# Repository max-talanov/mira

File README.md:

# MIRA

Исследовательская платформа для работы с мемристорными кроссбарами: чтение и программирование ячеек, формовка, умножение вектора на матрицу (VMM), спайковые модели.

Карты вставляются в слоты материнской платы. Сокет кроссбара стоит в центре, четыре карты AFE — квадратом вокруг него.

| Плата | Назначение | Проект KiCad |
|---|---|---|
| Mainboard | Материнская плата: слоты, линии каналов к сокету, разъём Zynq-модуля | [`hardware/Mainboard`](hardware/Mainboard/MIRA_Mainboard.kicad_pro) |
| AFE | Карта на 16 каналов с осциллографом тока. В комплекте четыре одинаковые карты | [`hardware/AFE`](hardware/AFE/MIRA_AFE.kicad_pro) |
| Zynq | Модуль с Zynq под сокетом: тайминг импульсов, сбор данных, USB 3 | [`hardware/Zynq`](hardware/Zynq/MIRA_Zynq.kicad_pro) |
| Crossbar | Сменная плата с сокетом под конкретный кроссбар | [`hardware/Crossbar`](hardware/Crossbar/MIRA_Crossbar.kicad_pro) |
| Forming | Карта формовки до ±10 В с ограничением тока | [`hardware/Forming`](hardware/Forming/MIRA_Forming.kicad_pro) |
| Power | Карта питания: вход 24 В, промежуточные шины, супервизор, аппаратные разрешения | [`hardware/Power`](hardware/Power/MIRA_Power.kicad_pro) |

Все 64 канала одинаковы и не привязаны к роли. Плата Crossbar сама решает, какие каналы будут BL, WL или NL. Например, на место 16×16×16 можно поставить кроссбар 32×8×8.

Требования и компоновка: [техническое задание](docs/ТЗ.md) и [3D-эскиз](docs/concept-3d.html).

Общие символы, footprint и 3D-модели лежат в [`hardware/libraries`](hardware/libraries). Каждый проект подключает их через `${KIPRJMOD}/../libraries`, поэтому папку `hardware/` нужно держать целиком.

## Версии

У каждой платы своя версия. Она хранится в переменной проекта `VERSION` (Файл → Свойства проекта → Текстовые переменные) и выводится в поле Rev штампа. Изменения описаны в `CHANGELOG.md` в папке платы.

| Версия | Когда повышать |
|---|---|
| 0.0.x | Небольшие изменения |
| 0.x.0 | Большие изменения |
| 1.0.0 | Плата доделана в KiCad |

Тег версии называется по плате, например `afe-v0.1.0`. Выпуск на производство учитывается отдельно и номер версии не меняет.

## Ветки

Каждая плата разрабатывается в своей ветке `board/<плата>`. Готовые шаги вливаются в `main` через PR.

## Лицензия

[LICENSE](LICENSE). Уведомления о сторонних библиотеках и моделях хранятся рядом с соответствующими файлами.

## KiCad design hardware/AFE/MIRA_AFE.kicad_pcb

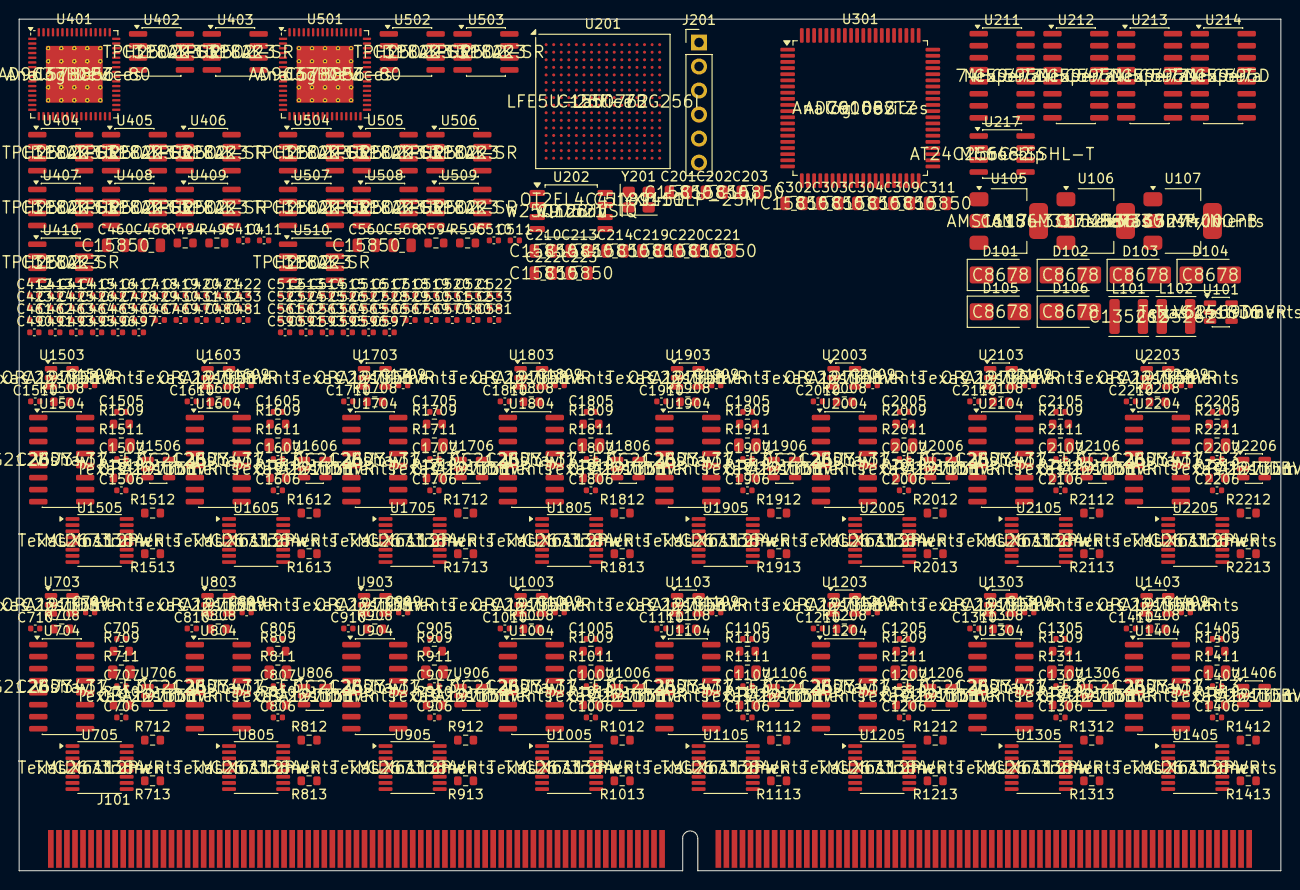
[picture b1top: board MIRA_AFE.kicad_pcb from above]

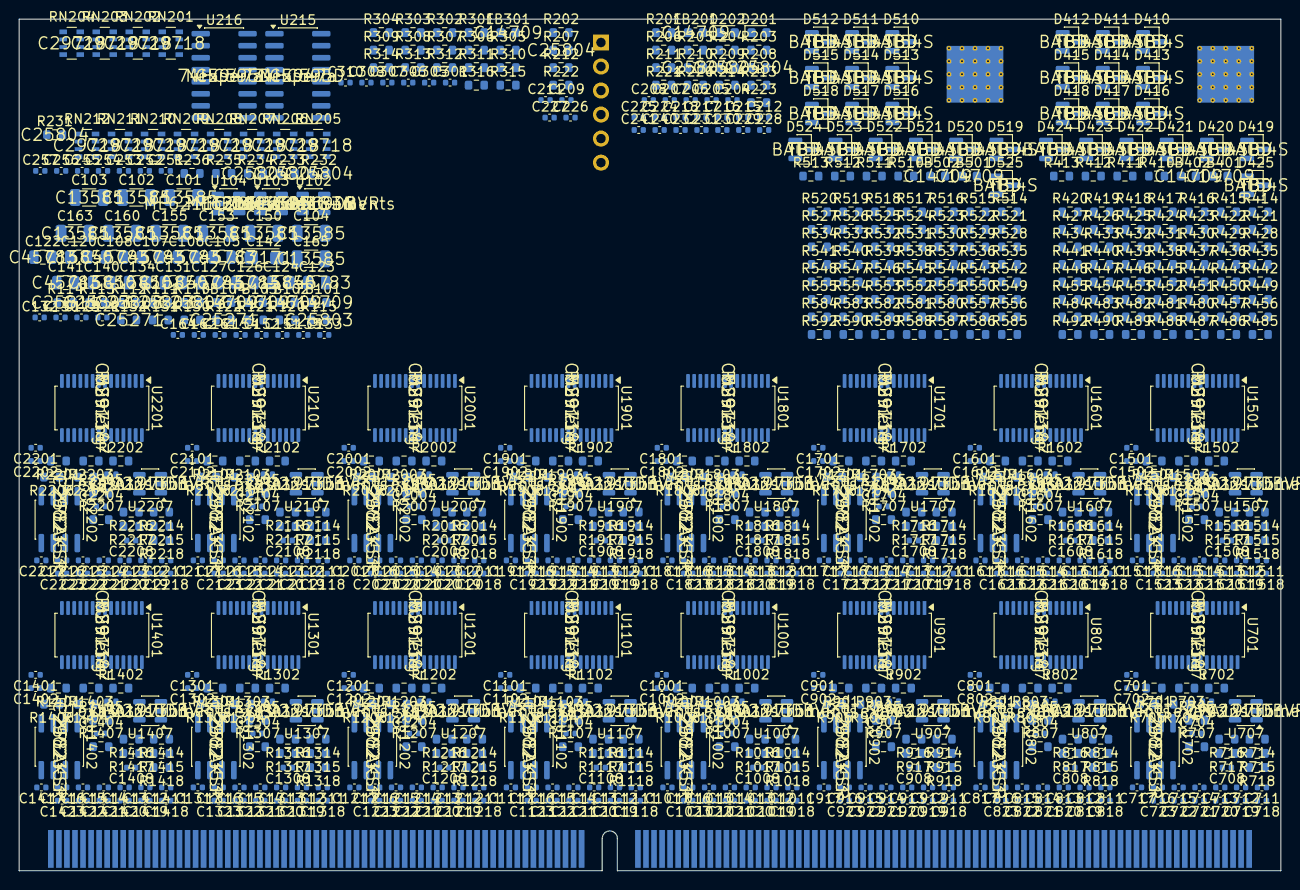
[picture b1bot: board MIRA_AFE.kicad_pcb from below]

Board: 6 copper layers, 133.3 x 90.0 mm, 1223 parts (834 on the bottom side), 771 nets, no tracks yet.

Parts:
C101, C102, C103, C104, C150, C153, C155, C160, C163, C165: 10u 50V; C_1206_3216Metric
C105, C106, C107, C108, C122, C123, C126, C127, C141: 22u; C_0805_2012Metric
C120, C124, C131, C134, C140, C201, C202, C203, C210, C213, C214, C219, C220, C221, C222, C223, C302, C303, C304, C309, C311, C460, C560: 10u; C_0805_2012Metric
C121, C125, C132, C135, C151, C154, C161, C164, C204, C205, C206, C207, C208, C209, C211, C212, C215, C216, C217, C218, C224, C225, C226, C227, C228, C229, C230, C231, C232, C240, C241, C251, C252, C253, C254, C255, C256, C257, C305, C306, C307, C308, C310, C412, C415, C418, C421, C424, C427, C430, C433, C461, C462, C463, C464, C465, C466, C467, C469, C470, C480, C481, C491, C493, C495, C496, C497, C512, C515, C518, C521, C524, C527, C530, C533, C561, C562, C563, C564, C565, C566, C567, C569, C570, C580, C581, C591, C593, C595, C596, C597, C701, C702, C703, C709, C710, C711, C712, C713, C714, C715, C716, C717, C718, C719, C720, C721, C722, C723, C801, C802, C803, C809, C810, C811, C812, C813, C814, C815, C816, C817, C818, C819, C820, C821, C822, C823, C901, C902, C903, C909, C910, C911, C912, C913, C914, C915, C916, C917, C918, C919, C920, C921, C922, C923, C1001, C1002, C1003, C1009, C1010, C1011, C1012, C1013, C1014, C1015, C1016, C1017, C1018, C1019, C1020, C1021, C1022, C1023, C1101, C1102, C1103, C1109, C1110, C1111, C1112, C1113, C1114, C1115, C1116, C1117, C1118, C1119, C1120, C1121, C1122, C1123, C1201, C1202, C1203, C1209, C1210, C1211, C1212, C1213, C1214, C1215, C1216, C1217, C1218, C1219, C1220, C1221, C1222, C1223, C1301, C1302, C1303, C1309, C1310, C1311, C1312, C1313, C1314, C1315, C1316, C1317, C1318, C1319, C1320, C1321, C1322, C1323, C1401, C1402, C1403, C1409, C1410, C1411, C1412, C1413, C1414, C1415, C1416, C1417, C1418, C1419, C1420, C1421, C1422, C1423, C1501, C1502, C1503, C1509, C1510, C1511, C1512, C1513, C1514, C1515, C1516, C1517, C1518, C1519, C1520, C1521, C1522, C1523, C1601, C1602, C1603, C1609, C1610, C1611, C1612, C1613, C1614, C1615, C1616, C1617, C1618, C1619, C1620, C1621, C1622, C1623, C1701, C1702, C1703, C1709, C1710, C1711, C1712, C1713, C1714, C1715, C1716, C1717, C1718, C1719, C1720, C1721, C1722, C1723, C1801, C1802, C1803, C1809, C1810, C1811, C1812, C1813, C1814, C1815, C1816, C1817, C1818, C1819, C1820, C1821, C1822, C1823, C1901, C1902, C1903, C1909, C1910, C1911, C1912, C1913, C1914, C1915, C1916, C1917, C1918, C1919, C1920, C1921, C1922, C1923, C2001, C2002, C2003, C2009, C2010, C2011, C2012, C2013, C2014, C2015, C2016, C2017, C2018, C2019, C2020, C2021, C2022, C2023, C2101, C2102, C2103, C2109, C2110, C2111, C2112, C2113, C2114, C2115, C2116, C2117, C2118, C2119, C2120, C2121, C2122, C2123, C2201, C2202, C2203, C2209, C2210, C2211, C2212, C2213, C2214, C2215, C2216, C2217, C2218, C2219, C2220, C2221, C2222, C2223: 100n; C_0402_1005Metric
C130, C133, C490, C590: 1u; C_0402_1005Metric
C142: 10u tant.; CP_EIA-3216-18_Kemet-A
C152, C162: 1u 25V; C_0402_1005Metric
C301: 100n X8R; C_0402_1005Metric
C410, C413, C416, C419, C422, C425, C428, C431, C510, C513, C516, C519, C522, C525, C528, C531: 22p C0G; C_0402_1005Metric
C411, C414, C417, C420, C423, C426, C429, C432, C511, C514, C517, C520, C523, C526, C529, C532: 150p C0G; C_0402_1005Metric
C468, C568: 4.7u; C_0805_2012Metric
C704, C804, C904, C1004, C1104, C1204, C1304, C1404, C1504, C1604, C1704, C1804, C1904, C2004, C2104, C2204: 2.2p C0G; C_0402_1005Metric
C705, C805, C905, C1005, C1105, C1205, C1305, C1405, C1505, C1605, C1705, C1805, C1905, C2005, C2105, C2205: 47p C0G; C_0402_1005Metric
C706, C806, C906, C1006, C1106, C1206, C1306, C1406, C1506, C1606, C1706, C1806, C1906, C2006, C2106, C2206: TBD; C_0402_1005Metric
C707, C807, C907, C1007, C1107, C1207, C1307, C1407, C1507, C1607, C1707, C1807, C1907, C2007, C2107, C2207: 0.5p C0G; C_0402_1005Metric
C708, C808, C908, C1008, C1108, C1208, C1308, C1408, C1508, C1608, C1708, C1808, C1908, C2008, C2108, C2208: 1n C0G; C_0402_1005Metric
D101, D102, D103, D104, D105, D106: SS34; D_SMA
D201, D202: green; LED_0603_1608Metric
D410, D411, D412, D413, D414, D415, D416, D417, D418, D419, D420, D421, D422, D423, D424, D425, D510, D511, D512, D513, D514, D515, D516, D517, D518, D519, D520, D521, D522, D523, D524, D525: BAT54S; SOT-23
FB101, FB102, FB103, FB104, FB201, FB301, FB401, FB402, FB501, FB502: BLM18PG121SN1D; L_0603_1608Metric
J101: DIMM-288 card edge; DIMM288_CardEdge
J201: JTAG_1x6; PinHeader_1x06_P2.54mm_Vertical
L101, L102: 2.2uH; L_Sunlord_SWPA4020S
R110, R111, R113, R115: 100k; R_0603_1608Metric
R112: 120k; R_0603_1608Metric
R114: 200k; R_0603_1608Metric
R120, R130: 120R 1%; R_0603_1608Metric
R121, R131: 1.33k 1%; R_0603_1608Metric
R122, R132: 1R; R_0603_1608Metric
R201, R202, R203, R204, R206, R211, R212, R213, R214, R235, R236: 4.7k; R_0603_1608Metric
R205, R222, R223, R301, R302, R303, R304, R305, R306, R307, R308, R309, R310, R311, R312, R313, R314, R315, R316, R481, R483, R485, R487, R489, R581, R583, R585, R587, R589, R713, R718, R813, R818, R913, R918, R1013, R1018, R1113, R1118, R1213, R1218, R1313, R1318, R1413, R1418, R1513, R1518, R1613, R1618, R1713, R1718, R1813, R1818, R1913, R1918, R2013, R2018, R2113, R2118, R2213, R2218: 1k; R_0603_1608Metric
R207, R208, R209, R210, R231, R232, R233, R234: 10k; R_0603_1608Metric
R220: 33R; R_0603_1608Metric
R221: 22R; R_0603_1608Metric
R410, R416, R422, R428, R434, R440, R446, R452, R495, R510, R516, R522, R528, R534, R540, R546, R552, R595: 10.7k 1%; R_0603_1608Metric
R411, R412, R413, R417, R418, R419, R423, R424, R425, R429, R430, R431, R435, R436, R437, R441, R442, R443, R447, R448, R449, R453, R454, R455, R494, R511, R512, R513, R517, R518, R519, R523, R524, R525, R529, R530, R531, R535, R536, R537, R541, R542, R543, R547, R548, R549, R553, R554, R555, R594: 1k 1%; R_0603_1608Metric
R414, R415, R420, R421, R426, R427, R432, R433, R438, R439, R444, R445, R450, R451, R456, R457, R514, R515, R520, R521, R526, R527, R532, R533, R538, R539, R544, R545, R550, R551, R556, R557: 49.9R; R_0603_1608Metric
R480, R580: 100R; R_0603_1608Metric
R482, R484, R486, R488, R490, R582, R584, R586, R588, R590: 1.2k; R_0603_1608Metric
R492, R592: 10k 1%; R_0603_1608Metric
R701, R801, R901, R1001, R1101, R1201, R1301, R1401, R1501, R1601, R1701, R1801, R1901, R2001, R2101, R2201: 19.1k 1%; R_0603_1608Metric
R702, R703, R802, R803, R902, R903, R1002, R1003, R1102, R1103, R1202, R1203, R1302, R1303, R1402, R1403, R1502, R1503, R1602, R1603, R1702, R1703, R1802, R1803, R1902, R1903, R2002, R2003, R2102, R2103, R2202, R2203: 499 0.1%; R_0603_1608Metric
R704, R706, R714, R715, R716, R717, R804, R806, R814, R815, R816, R817, R904, R906, R914, R915, R916, R917, R1004, R1006, R1014, R1015, R1016, R1017, R1104, R1106, R1114, R1115, R1116, R1117, R1204, R1206, R1214, R1215, R1216, R1217, R1304, R1306, R1314, R1315, R1316, R1317, R1404, R1406, R1414, R1415, R1416, R1417, R1504, R1506, R1514, R1515, R1516, R1517, R1604, R1606, R1614, R1615, R1616, R1617, R1704, R1706, R1714, R1715, R1716, R1717, R1804, R1806, R1814, R1815, R1816, R1817, R1904, R1906, R1914, R1915, R1916, R1917, R2004, R2006, R2014, R2015, R2016, R2017, R2104, R2106, R2114, R2115, R2116, R2117, R2204, R2206, R2214, R2215, R2216, R2217: 10k 0.1%; R_0603_1608Metric
R705, R707, R805, R807, R905, R907, R1005, R1007, R1105, R1107, R1205, R1207, R1305, R1307, R1405, R1407, R1505, R1507, R1605, R1607, R1705, R1707, R1805, R1807, R1905, R1907, R2005, R2007, R2105, R2107, R2205, R2207: 24.9k 0.1%; R_0603_1608Metric
R708, R808, R908, R1008, R1108, R1208, R1308, R1408, R1508, R1608, R1708, R1808, R1908, R2008, R2108, R2208: 1k 0.1%; R_0603_1608Metric
R709, R809, R909, R1009, R1109, R1209, R1309, R1409, R1509, R1609, R1709, R1809, R1909, R2009, R2109, R2209: 20k 0.1%; R_0603_1608Metric
R710, R810, R910, R1010, R1110, R1210, R1310, R1410, R1510, R1610, R1710, R1810, R1910, R2010, R2110, R2210: 2M 0.1%; R_0603_1608Metric
R711, R811, R911, R1011, R1111, R1211, R1311, R1411, R1511, R1611, R1711, R1811, R1911, R2011, R2111, R2211: 200M 1%; R_0805_2012Metric
R712, R812, R912, R1012, R1112, R1212, R1312, R1412, R1512, R1612, R1712, R1812, R1912, R2012, R2112, R2212: 10M; R_0603_1608Metric
RN201, RN202, RN203, RN204, RN205, RN206, RN207, RN208, RN209, RN210, RN211, RN212: 10k ×4; R_Array_Convex_4x0603
U101, U102: TLV62569DBVR; SOT-23-5
U103: ME6211C25M5G-N; SOT-23-5
U104: ME6211C28M5G-N; SOT-23-5
U105: AMS1117-3.3; SOT-223-3_TabPin2
U106: LM317MBSTT3G; SOT-223-3_TabPin2
U107: LM337IMP/NOPB; SOT-223-3_TabPin2
U201: LFE5U-25F-7BG256I; BGA-256_14.0x14.0mm_Layout16x16_P0.8mm_Ball0.45mm_Pad0.32mm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
U202: W25Q128JVSIQ; SOIC-8_5.3x5.3mm_P1.27mm
U211, U212, U213, U214, U215, U216: 74HC595D; SOIC-16_3.9x9.9mm_P1.27mm
U217: AT24C256C-SSHL-T; SOIC-8_3.9x4.9mm_P1.27mm
U301: AD7616BSTZ; LQFP-80_14x14mm_P0.65mm
U401, U501: AD9637BCPZ-80; QFN-64-1EP_9x9mm_P0.5mm_EP6x6mm_ThermalVias
U402, U403, U404, U405, U406, U407, U408, U409, U410, U502, U503, U504, U505, U506, U507, U508, U509, U510: TPH2502-SR; SOIC-8_3.9x4.9mm_P1.27mm
U701, U801, U901, U1001, U1101, U1201, U1301, U1401, U1501, U1601, U1701, U1801, U1901, U2001, U2101, U2201: MS9714; TSSOP-28_4.4x9.7mm_P0.65mm
U702, U802, U902, U1002, U1102, U1202, U1302, U1402, U1502, U1602, U1702, U1802, U1902, U2002, U2102, U2202: TP2582-SR; SOIC-8_3.9x4.9mm_P1.27mm
U703, U706, U707, U803, U806, U807, U903, U906, U907, U1003, U1006, U1007, U1103, U1106, U1107, U1203, U1206, U1207, U1303, U1306, U1307, U1403, U1406, U1407, U1503, U1506, U1507, U1603, U1606, U1607, U1703, U1706, U1707, U1803, U1806, U1807, U1903, U1906, U1907, U2003, U2006, U2007, U2103, U2106, U2107, U2203, U2206, U2207: OPA197IDBVR; SOT-23-5
U704, U804, U904, U1004, U1104, U1204, U1304, U1404, U1504, U1604, U1704, U1804, U1904, U2004, U2104, U2204: DG212BDY-T1-E3; SOIC-16_3.9x9.9mm_P1.27mm
U705, U805, U905, U1005, U1105, U1205, U1305, U1405, U1505, U1605, U1705, U1805, U1905, U2005, U2105, U2205: TMUX6112PWR; TSSOP-16_4.4x5mm_P0.65mm
Y201: OT2EL4C4JI-111OLP-25M; Oscillator_SMD_Abracon_ASE-4Pin_3.2x2.5mm

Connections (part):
+1V1: C122.1, C123.1, C201.1, C202.1, C203.1, C204.1, C205.1, C206.1, C207.1, C208.1, C209.1, L101.2, R111.1, U201.G6, U201.G7, U201.G9, U201.L8, U201.L9, U201.L10
+1V8: C126.1, C127.1, FB401.2, FB402.2, FB501.2, FB502.2, L102.2, R114.1
+2V5: C131.1, C132.1, C213.1, C214.1, C215.1, C216.1, C217.1, C218.1, FB201.1, U103.5, U201.H6, U201.H7, U201.H11, U201.J11
+2V8: C134.1, C135.1, C412.1, C415.1, C418.1, C421.1, C424.1, C427.1, C430.1, C433.1, C497.1, C512.1, C515.1, C518.1, C521.1, C524.1, C527.1, C530.1, C533.1, C597.1, U104.5, U402.8, U403.8, U404.8, U405.8, U406.8, U407.8, U408.8, U409.8, U410.8, U502.8, U503.8, U504.8, U505.8, U506.8, U507.8, U508.8, U509.8, U510.8
+3.3VA: C141.1, C142.1, C702.2, C722.1, C723.1, C802.2, C822.1, C823.1, C902.2, C922.1, C923.1, C1002.2, C1022.1, C1023.1, C1102.2, C1122.1, C1123.1, C1202.2, C1222.1, C1223.1, C1302.2, C1322.1, C1323.1, C1402.2, C1422.1, C1423.1, C1502.2, C1522.1, C1523.1, C1602.2, C1622.1, C1623.1, C1702.2, C1722.1, C1723.1, C1802.2, C1822.1, C1823.1, C1902.2, C1922.1, C1923.1, C2002.2, C2022.1, C2023.1, C2102.2, C2122.1, C2123.1, C2202.2, C2222.1, C2223.1, U105.2, U701.24, U701.27, U801.24, U801.27, U901.24, U901.27, U1001.24, U1001.27, U1101.24, U1101.27, U1201.24, U1201.27, U1301.24, U1301.27, U1401.24, U1401.27, U1501.24, U1501.27, U1601.24, U1601.27, U1701.24, U1701.27, U1801.24, U1801.27, U1901.24, U1901.27, U2001.24, U2001.27, U2101.24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
+3V3: C107.1, C108.1, C130.1, C133.1, C219.1, C220.1, C221.1, C222.1, C223.1, C224.1, C225.1, C226.1, C227.1, C228.1, C229.1, C230.1, C231.1, C232.1, C240.2, C241.1, C251.1, C252.1, C253.1, C254.1, C255.1, C256.1, C257.1, C310.1, C311.1, D104.1, FB104.2, J201.1, R201.1, R202.1, R203.1, R204.1, R205.1, R206.1, R207.1, R208.1, R209.1, R210.1, R211.1, R212.1, R213.1, R231.1, R232.1, R233.1, R234.1, R235.1, R236.1, U103.1, U103.3, U104.1, U104.3, U201.F6, U201.F7, U201.F10, U201.F11, U201.J6, U201.J7, U201.K11, U201.L6, U201.L11, U202.8, U211.10, U211.16, U212.10, U212.16, U213.10, U213.16, U214.10, U214.16, U215.10, U215.16, U216.10, U216.16, U217.8, U301.35, U301.40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
+5V: C105.1, C106.1, C120.1, C121.1, C124.1, C125.1, C140.1, C721.1, C821.1, C921.1, C1021.1, C1121.1, C1221.1, C1321.1, C1421.1, C1521.1, C1621.1, C1721.1, C1821.1, C1921.1, C2021.1, C2121.1, C2221.1, D103.1, FB103.2, FB301.1, R110.1, R113.1, U101.4, U102.4, U105.3, U704.12, U804.12, U904.12, U1004.12, U1104.12, U1204.12, U1304.12, U1404.12, U1504.12, U1604.12, U1704.12, U1804.12, U1904.12, U2004.12, U2104.12, U2204.12
+5VA: C305.1, C306.1, C307.1, C308.1, C309.1, FB301.2, U301.6, U301.15, U301.30, U301.71
+15V: C153.1, C154.1, C709.1, C711.1, C713.1, C715.1, C717.1, C719.1, C809.1, C811.1, C813.1, C815.1, C817.1, C819.1, C909.1, C911.1, C913.1, C915.1, C917.1, C919.1, C1009.1, C1011.1, C1013.1, C1015.1, C1017.1, C1019.1, C1109.1, C1111.1, C1113.1, C1115.1, C1117.1, C1119.1, C1209.1, C1211.1, C1213.1, C1215.1, C1217.1, C1219.1, C1309.1, C1311.1, C1313.1, C1315.1, C1317.1, C1319.1, C1409.1, C1411.1, C1413.1, C1415.1, C1417.1, C1419.1, C1509.1, C1511.1, C1513.1, C1515.1, C1517.1, C1519.1, C1609.1, C1611.1, C1613.1, C1615.1, C1617.1, C1619.1, C1709.1, C1711.1, C1713.1, C1715.1, C1717.1, C1719.1, C1809.1, C1811.1, C1813.1, C1815.1, C1817.1, C1819.1, C1909.1, C1911.1, C1913.1, C1915.1, C1917.1, C1919.1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
-15V: C163.1, C164.1, C710.2, C712.2, C714.2, C716.2, C718.2, C720.2, C810.2, C812.2, C814.2, C816.2, C818.2, C820.2, C910.2, C912.2, C914.2, C916.2, C918.2, C920.2, C1010.2, C1012.2, C1014.2, C1016.2, C1018.2, C1020.2, C1110.2, C1112.2, C1114.2, C1116.2, C1118.2, C1120.2, C1210.2, C1212.2, C1214.2, C1216.2, C1218.2, C1220.2, C1310.2, C1312.2, C1314.2, C1316.2, C1318.2, C1320.2, C1410.2, C1412.2, C1414.2, C1416.2, C1418.2, C1420.2, C1510.2, C1512.2, C1514.2, C1516.2, C1518.2, C1520.2, C1610.2, C1612.2, C1614.2, C1616.2, C1618.2, C1620.2, C1710.2, C1712.2, C1714.2, C1716.2, C1718.2, C1720.2, C1810.2, C1812.2, C1814.2, C1816.2, C1818.2, C1820.2, C1910.2, C1912.2, C1914.2, C1916.2, C1918.2, C1920.2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
/Channels/BLEED0: U201.L16, U705.9
/Channels/BLEED1: U201.L15, U805.9
/Channels/BLEED2: U201.M16, U905.9
/Channels/BLEED3: U201.M15, U1005.9
/Channels/BLEED4: U201.K13, U1105.9
/Channels/BLEED5: U201.K12, U1205.9
/Channels/BLEED6: U201.L13, U1305.9
/Channels/BLEED7: U201.L12, U1405.9
/Channels/BLEED8: U201.N16, U1505.9
/Channels/BLEED9: U201.P15, U1605.9
/Channels/BLEED10: U201.L14, U1705.9
/Channels/BLEED11: U201.M14, U1805.9
/Channels/BLEED12: U201.P16, U1905.9
/Channels/BLEED13: U201.R16, U2005.9
/Channels/BLEED14: U201.M13, U2105.9
/Channels/BLEED15: U201.N14, U2205.9
/Channels/CH0/F: C705.2, C706.2, C707.2, R708.2, R709.2, R710.2, R711.2, R712.2, U705.3, U706.3
/Channels/CH0/FB: R714.1, U706.1, U706.4
/Channels/CH0/IA: R702.1, R706.1, U701.22
/Channels/CH0/IB: R703.1, R704.1, U701.21
/Channels/CH0/OUT: C707.1, R711.1, R716.1, U703.1, U704.3, U704.11, U704.14
/Channels/CH0/SENSE: R712.1, U703.4, U705.14
/Channels/CH0/VSET: C704.2, R705.2, U702.1, U703.3
/Channels/CH1/F: C805.2, C806.2, C807.2, R808.2, R809.2, R810.2, R811.2, R812.2, U805.3, U806.3
/Channels/CH1/FB: R814.1, U806.1, U806.4
/Channels/CH1/IA: R802.1, R806.1, U801.22
/Channels/CH1/IB: R803.1, R804.1, U801.21
/Channels/CH1/OUT: C807.1, R811.1, R816.1, U803.1, U804.3, U804.11, U804.14
/Channels/CH1/SENSE: R812.1, U803.4, U805.14
/Channels/CH1/VSET: C804.2, R805.2, U802.1, U803.3
/Channels/CH2/F: C905.2, C906.2, C907.2, R908.2, R909.2, R910.2, R911.2, R912.2, U905.3, U906.3
/Channels/CH2/FB: R914.1, U906.1, U906.4
/Channels/CH2/IA: R902.1, R906.1, U901.22
/Channels/CH2/IB: R903.1, R904.1, U901.21
/Channels/CH2/OUT: C907.1, R911.1, R916.1, U903.1, U904.3, U904.11, U904.14
/Channels/CH2/SENSE: R912.1, U903.4, U905.14
/Channels/CH2/VSET: C904.2, R905.2, U902.1, U903.3
/Channels/CH3/F: C1005.2, C1006.2, C1007.2, R1008.2, R1009.2, R1010.2, R1011.2, R1012.2, U1005.3, U1006.3
/Channels/CH3/FB: R1014.1, U1006.1, U1006.4
/Channels/CH3/IA: R1002.1, R1006.1, U1001.22
/Channels/CH3/IB: R1003.1, R1004.1, U1001.21
/Channels/CH3/OUT: C1007.1, R1011.1, R1016.1, U1003.1, U1004.3, U1004.11, U1004.14
/Channels/CH3/SENSE: R1012.1, U1003.4, U1005.14
/Channels/CH3/VSET: C1004.2, R1005.2, U1002.1, U1003.3
/Channels/CH4/F: C1105.2, C1106.2, C1107.2, R1108.2, R1109.2, R1110.2, R1111.2, R1112.2, U1105.3, U1106.3
/Channels/CH4/FB: R1114.1, U1106.1, U1106.4
/Channels/CH4/IA: R1102.1, R1106.1, U1101.22
/Channels/CH4/IB: R1103.1, R1104.1, U1101.21
/Channels/CH4/OUT: C1107.1, R1111.1, R1116.1, U1103.1, U1104.3, U1104.11, U1104.14
/Channels/CH4/SENSE: R1112.1, U1103.4, U1105.14
/Channels/CH4/VSET: C1104.2, R1105.2, U1102.1, U1103.3
/Channels/CH5/F: C1205.2, C1206.2, C1207.2, R1208.2, R1209.2, R1210.2, R1211.2, R1212.2, U1205.3, U1206.3
/Channels/CH5/FB: R1214.1, U1206.1, U1206.4
/Channels/CH5/IA: R1202.1, R1206.1, U1201.22
/Channels/CH5/IB: R1203.1, R1204.1, U1201.21
/Channels/CH5/OUT: C1207.1, R1211.1, R1216.1, U1203.1, U1204.3, U1204.11, U1204.14
/Channels/CH5/SENSE: R1212.1, U1203.4, U1205.14
/Channels/CH5/VSET: C1204.2, R1205.2, U1202.1, U1203.3
/Channels/CH6/F: C1305.2, C1306.2, C1307.2, R1308.2, R1309.2, R1310.2, R1311.2, R1312.2, U1305.3, U1306.3
/Channels/CH6/FB: R1314.1, U1306.1, U1306.4
/Channels/CH6/IA: R1302.1, R1306.1, U1301.22
/Channels/CH6/IB: R1303.1, R1304.1, U1301.21
/Channels/CH6/OUT: C1307.1, R1311.1, R1316.1, U1303.1, U1304.3, U1304.11, U1304.14
/Channels/CH6/SENSE: R1312.1, U1303.4, U1305.14
/Channels/CH6/VSET: C1304.2, R1305.2, U1302.1, U1303.3
/Channels/CH7/F: C1405.2, C1406.2, C1407.2, R1408.2, R1409.2, R1410.2, R1411.2, R1412.2, U1405.3, U1406.3
/Channels/CH7/FB: R1414.1, U1406.1, U1406.4
/Channels/CH7/IA: R1402.1, R1406.1, U1401.22
/Channels/CH7/IB: R1403.1, R1404.1, U1401.21
/Channels/CH7/OUT: C1407.1, R1411.1, R1416.1, U1403.1, U1404.3, U1404.11, U1404.14
/Channels/CH7/SENSE: R1412.1, U1403.4, U1405.14
/Channels/CH7/VSET: C1404.2, R1405.2, U1402.1, U1403.3
/Channels/CH8/F: C1505.2, C1506.2, C1507.2, R1508.2, R1509.2, R1510.2, R1511.2, R1512.2, U1505.3, U1506.3
/Channels/CH8/FB: R1514.1, U1506.1, U1506.4
/Channels/CH8/IA: R1502.1, R1506.1, U1501.22
/Channels/CH8/IB: R1503.1, R1504.1, U1501.21
/Channels/CH8/OUT: C1507.1, R1511.1, R1516.1, U1503.1, U1504.3, U1504.11, U1504.14
/Channels/CH8/SENSE: R1512.1, U1503.4, U1505.14
/Channels/CH8/VSET: C1504.2, R1505.2, U1502.1, U1503.3
/Channels/CH9/F: C1605.2, C1606.2, C1607.2, R1608.2, R1609.2, R1610.2, R1611.2, R1612.2, U1605.3, U1606.3
/Channels/CH9/FB: R1614.1, U1606.1, U1606.4
/Channels/CH9/IA: R1602.1, R1606.1, U1601.22
/Channels/CH9/IB: R1603.1, R1604.1, U1601.21
/Channels/CH9/OUT: C1607.1, R1611.1, R1616.1, U1603.1, U1604.3, U1604.11, U1604.14
/Channels/CH9/SENSE: R1612.1, U1603.4, U1605.14
/Channels/CH9/VSET: C1604.2, R1605.2, U1602.1, U1603.3
/Channels/CH10/F: C1705.2, C1706.2, C1707.2, R1708.2, R1709.2, R1710.2, R1711.2, R1712.2, U1705.3, U1706.3
/Channels/CH10/FB: R1714.1, U1706.1, U1706.4
/Channels/CH10/IA: R1702.1, R1706.1, U1701.22
/Channels/CH10/IB: R1703.1, R1704.1, U1701.21
/Channels/CH10/OUT: C1707.1, R1711.1, R1716.1, U1703.1, U1704.3, U1704.11, U1704.14
/Channels/CH10/SENSE: R1712.1, U1703.4, U1705.14
/Channels/CH10/VSET: C1704.2, R1705.2, U1702.1, U1703.3
/Channels/CH11/F: C1805.2, C1806.2, C1807.2, R1808.2, R1809.2, R1810.2, R1811.2, R1812.2, U1805.3, U1806.3
/Channels/CH11/FB: R1814.1, U1806.1, U1806.4
/Channels/CH11/IA: R1802.1, R1806.1, U1801.22
/Channels/CH11/IB: R1803.1, R1804.1, U1801.21
/Channels/CH11/OUT: C1807.1, R1811.1, R1816.1, U1803.1, U1804.3, U1804.11, U1804.14
/Channels/CH11/SENSE: R1812.1, U1803.4, U1805.14
/Channels/CH11/VSET: C1804.2, R1805.2, U1802.1, U1803.3
/Channels/CH12/F: C1905.2, C1906.2, C1907.2, R1908.2, R1909.2, R1910.2, R1911.2, R1912.2, U1905.3, U1906.3
/Channels/CH12/FB: R1914.1, U1906.1, U1906.4
/Channels/CH12/IA: R1902.1, R1906.1, U1901.22
/Channels/CH12/IB: R1903.1, R1904.1, U1901.21
/Channels/CH12/OUT: C1907.1, R1911.1, R1916.1, U1903.1, U1904.3, U1904.11, U1904.14
/Channels/CH12/SENSE: R1912.1, U1903.4, U1905.14
/Channels/CH12/VSET: C1904.2, R1905.2, U1902.1, U1903.3
/Channels/CH13/F: C2005.2, C2006.2, C2007.2, R2008.2, R2009.2, R2010.2, R2011.2, R2012.2, U2005.3, U2006.3
/Channels/CH13/FB: R2014.1, U2006.1, U2006.4
/Channels/CH13/IA: R2002.1, R2006.1, U2001.22
/Channels/CH13/IB: R2003.1, R2004.1, U2001.21
/Channels/CH13/OUT: C2007.1, R2011.1, R2016.1, U2003.1, U2004.3, U2004.11, U2004.14
/Channels/CH13/SENSE: R2012.1, U2003.4, U2005.14
/Channels/CH13/VSET: C2004.2, R2005.2, U2002.1, U2003.3
/Channels/CH14/F: C2105.2, C2106.2, C2107.2, R2108.2, R2109.2, R2110.2, R2111.2, R2112.2, U2105.3, U2106.3
/Channels/CH14/FB: R2114.1, U2106.1, U2106.4
/Channels/CH14/IA: R2102.1, R2106.1, U2101.22
/Channels/CH14/IB: R2103.1, R2104.1, U2101.21
/Channels/CH14/OUT: C2107.1, R2111.1, R2116.1, U2103.1, U2104.3, U2104.11, U2104.14
/Channels/CH14/SENSE: R2112.1, U2103.4, U2105.14
/Channels/CH14/VSET: C2104.2, R2105.2, U2102.1, U2103.3
/Channels/CH15/F: C2205.2, C2206.2, C2207.2, R2208.2, R2209.2, R2210.2, R2211.2, R2212.2, U2205.3, U2206.3
/Channels/CH15/FB: R2214.1, U2206.1, U2206.4
/Channels/CH15/IA: R2202.1, R2206.1, U2201.22
/Channels/CH15/IB: R2203.1, R2204.1, U2201.21
/Channels/CH15/OUT: C2207.1, R2211.1, R2216.1, U2203.1, U2204.3, U2204.11, U2204.14
/Channels/CH15/SENSE: R2212.1, U2203.4, U2205.14
/Channels/CH15/VSET: C2204.2, R2205.2, U2202.1, U2203.3
/Channels/CONN0: U201.L1, U705.1, U705.16
/Channels/CONN1: U201.L2, U805.1, U805.16
/Channels/CONN2: U201.M1, U905.1, U905.16
/Channels/CONN3: U201.M2, U1005.1, U1005.16
/Channels/CONN4: U201.K4, U1105.1, U1105.16
/Channels/CONN5: U201.K5, U1205.1, U1205.16
/Channels/CONN6: U201.L4, U1305.1, U1305.16
/Channels/CONN7: U201.L5, U1405.1, U1405.16
/Channels/CONN8: U201.N1, U1505.1, U1505.16
/Channels/CONN9: U201.P2, U1605.1, U1605.16
/Channels/CONN10: U201.L3, U1705.1, U1705.16
/Channels/CONN11: U201.M3, U1805.1, U1805.16
/Channels/CONN12: U201.P1, U1905.1, U1905.16
/Channels/CONN13: U201.R1, U2005.1, U2005.16
/Channels/CONN14: U201.M4, U2105.1, U2105.16
/Channels/CONN15: U201.N3, U2205.1, U2205.16
/Channels/DAC_A0: U201.E8, U701.14, U801.14, U901.14, U1001.14, U1101.14, U1201.14, U1301.14, U1401.14
/Channels/DAC_A1: U201.D8, U701.13, U801.13, U901.13, U1001.13, U1101.13, U1201.13, U1301.13, U1401.13
/Channels/DAC_A2: U201.C8, U701.12, U801.12, U901.12, U1001.12, U1101.12, U1201.12, U1301.12, U1401.12
/Channels/DAC_A3: U201.B8, U701.11, U801.11, U901.11, U1001.11, U1101.11, U1201.11, U1301.11, U1401.11
/Channels/DAC_A4: U201.B9, U701.10, U801.10, U901.10, U1001.10, U1101.10, U1201.10, U1301.10, U1401.10
/Channels/DAC_A5: U201.C9, U701.9, U801.9, U901.9, U1001.9, U1101.9, U1201.9, U1301.9, U1401.9
/Channels/DAC_A6: U201.D9, U701.8, U801.8, U901.8, U1001.8, U1101.8, U1201.8, U1301.8, U1401.8
/Channels/DAC_A7: U201.E9, U701.7, U801.7, U901.7, U1001.7, U1101.7, U1201.7, U1301.7, U1401.7
/Channels/DAC_A8: U201.A9, U701.6, U801.6, U901.6, U1001.6, U1101.6, U1201.6, U1301.6, U1401.6
/Channels/DAC_A9: U201.A10, U701.5, U801.5, U901.5, U1001.5, U1101.5, U1201.5, U1301.5, U1401.5
/Channels/DAC_A10: U201.B10, U701.4, U801.4, U901.4, U1001.4, U1101.4, U1201.4, U1301.4, U1401.4
/Channels/DAC_A11: U201.C10, U701.3, U801.3, U901.3, U1001.3, U1101.3, U1201.3, U1301.3, U1401.3
/Channels/DAC_A12: U201.D10, U701.2, U801.2, U901.2, U1001.2, U1101.2, U1201.2, U1301.2, U1401.2
/Channels/DAC_A13: U201.E10, U701.1, U801.1, U901.1, U1001.1, U1101.1, U1201.1, U1301.1, U1401.1
/Channels/DAC_B0: U201.D11, U1501.14, U1601.14, U1701.14, U1801.14, U1901.14, U2001.14, U2101.14, U2201.14
/Channels/DAC_B1: U201.E11, U1501.13, U1601.13, U1701.13, U1801.13, U1901.13, U2001.13, U2101.13, U2201.13
/Channels/DAC_B2: U201.A11, U1501.12, U1601.12, U1701.12, U1801.12, U1901.12, U2001.12, U2101.12, U2201.12
/Channels/DAC_B3: U201.A12, U1501.11, U1601.11, U1701.11, U1801.11, U1901.11, U2001.11, U2101.11, U2201.11
/Channels/DAC_B4: U201.B12, U1501.10, U1601.10, U1701.10, U1801.10, U1901.10, U2001.10, U2101.10, U2201.10
/Channels/DAC_B5: U201.C12, U1501.9, U1601.9, U1701.9, U1801.9, U1901.9, U2001.9, U2101.9, U2201.9
/Channels/DAC_B6: U201.D12, U1501.8, U1601.8, U1701.8, U1801.8, U1901.8, U2001.8, U2101.8, U2201.8
/Channels/DAC_B7: U201.E12, U1501.7, U1601.7, U1701.7, U1801.7, U1901.7, U2001.7, U2101.7, U2201.7
/Channels/DAC_B8: U201.B13, U1501.6, U1601.6, U1701.6, U1801.6, U1901.6, U2001.6, U2101.6, U2201.6
/Channels/DAC_B9: U201.C13, U1501.5, U1601.5, U1701.5, U1801.5, U1901.5, U2001.5, U2101.5, U2201.5
/Channels/DAC_B10: U201.D13, U1501.4, U1601.4, U1701.4, U1801.4, U1901.4, U2001.4, U2101.4, U2201.4
/Channels/DAC_B11: U201.E13, U1501.3, U1601.3, U1701.3, U1801.3, U1901.3, U2001.3, U2101.3, U2201.3
/Channels/DAC_B12: U201.A13, U1501.2, U1601.2, U1701.2, U1801.2, U1901.2, U2001.2, U2101.2, U2201.2
/Channels/DAC_B13: U201.A14, U1501.1, U1601.1, U1701.1, U1801.1, U1901.1, U2001.1, U2101.1, U2201.1
/Channels/DAC_CLK0: U201.A2, U701.28
/Channels/DAC_CLK1: U201.B3, U801.28
/Channels/DAC_CLK2: U201.A3, U901.28
/Channels/DAC_CLK3: U201.A4, U1001.28
/Channels/DAC_CLK4: U201.E4, U1101.28
/Channels/DAC_CLK5: U201.D4, U1201.28
/Channels/DAC_CLK6: U201.C4, U1301.28
/Channels/DAC_CLK7: U201.B4, U1401.28
/Channels/DAC_CLK8: U201.E5, U1501.28
/Channels/DAC_CLK9: U201.D5, U1601.28
/Channels/DAC_CLK10: U201.C5, U1701.28
/Channels/DAC_CLK11: U201.B5, U1801.28
/Channels/DAC_CLK12: U201.A5, U1901.28
/Channels/DAC_CLK13: U201.A6, U2001.28
/Channels/DAC_CLK14: U201.E6, U2101.28
/Channels/DAC_CLK15: U201.D6, U2201.28
/Channels/I_SLOW0: C708.1, R718.2, U301.28
/Channels/I_SLOW1: C808.1, R818.2, U301.26
/Channels/I_SLOW2: C908.1, R918.2, U301.24
/Channels/I_SLOW3: C1008.1, R1018.2, U301.22
/Channels/I_SLOW4: C1108.1, R1118.2, U301.19
/Channels/I_SLOW5: C1208.1, R1218.2, U301.17
/Channels/I_SLOW6: C1308.1, R1318.2, U301.14
/Channels/I_SLOW7: C1408.1, R1418.2, U301.12
/Channels/I_SLOW8: C1508.1, R1518.2, U301.73
/Channels/I_SLOW9: C1608.1, R1618.2, U301.75
/Channels/I_SLOW10: C1708.1, R1718.2, U301.77
/Channels/I_SLOW11: C1808.1, R1818.2, U301.79
/Channels/I_SLOW12: C1908.1, R1918.2, U301.2
/Channels/I_SLOW13: C2008.1, R2018.2, U301.4
/Channels/I_SLOW14: C2108.1, R2118.2, U301.7
/Channels/I_SLOW15: C2208.1, R2218.2, U301.9
/Channels/LINE0: J101.21, R713.1, U705.2, U705.15
/Channels/LINE1: J101.25, R813.1, U805.2, U805.15
/Channels/LINE2: J101.29, R913.1, U905.2, U905.15
/Channels/LINE3: J101.33, R1013.1, U1005.2, U1005.15
/Channels/LINE4: J101.37, R1113.1, U1105.2, U1105.15
/Channels/LINE5: J101.41, R1213.1, U1205.2, U1205.15
/Channels/LINE6: J101.45, R1313.1, U1305.2, U1305.15
/Channels/LINE7: J101.49, R1413.1, U1405.2, U1405.15
/Channels/LINE8: J101.53, R1513.1, U1505.2, U1505.15
/Channels/LINE9: J101.57, R1613.1, U1605.2, U1605.15
/Channels/LINE10: J101.61, R1713.1, U1705.2, U1705.15
/Channels/LINE11: J101.65, R1813.1, U1805.2, U1805.15
/Channels/LINE12: J101.69, R1913.1, U1905.2, U1905.15
/Channels/LINE13: J101.73, R2013.1, U2005.2, U2005.15
/Channels/LINE14: J101.77, R2113.1, U2105.2, U2105.15
/Channels/LINE15: J101.81, R2213.1, U2205.2, U2205.15
/Channels/RNG1_0: RN201.1, U211.15, U704.1
/Channels/RNG1_1: RN201.2, U211.1, U804.1
/Channels/RNG1_2: RN201.3, U211.2, U904.1
/Channels/RNG1_3: RN201.4, U211.3, U1004.1
/Channels/RNG1_4: RN202.1, U211.4, U1104.1
/Channels/RNG1_5: RN202.2, U211.5, U1204.1
/Channels/RNG1_6: RN202.3, U211.6, U1304.1
/Channels/RNG1_7: RN202.4, U211.7, U1404.1
/Channels/RNG1_8: RN203.1, U212.15, U1504.1
/Channels/RNG1_9: RN203.2, U212.1, U1604.1
/Channels/RNG1_10: RN203.3, U212.2, U1704.1
/Channels/RNG1_11: RN203.4, U212.3, U1804.1
/Channels/RNG1_12: RN204.1, U212.4, U1904.1
/Channels/RNG1_13: RN204.2, U212.5, U2004.1
/Channels/RNG1_14: RN204.3, U212.6, U2104.1
/Channels/RNG1_15: RN204.4, U212.7, U2204.1
/Channels/RNG2_0: RN205.1, U213.15, U704.16
/Channels/RNG2_1: RN205.2, U213.1, U804.16
/Channels/RNG2_2: RN205.3, U213.2, U904.16
/Channels/RNG2_3: RN205.4, U213.3, U1004.16
/Channels/RNG2_4: RN206.1, U213.4, U1104.16
/Channels/RNG2_5: RN206.2, U213.5, U1204.16
/Channels/RNG2_6: RN206.3, U213.6, U1304.16
/Channels/RNG2_7: RN206.4, U213.7, U1404.16
/Channels/RNG2_8: RN207.1, U214.15, U1504.16
/Channels/RNG2_9: RN207.2, U214.1, U1604.16
/Channels/RNG2_10: RN207.3, U214.2, U1704.16
/Channels/RNG2_11: RN207.4, U214.3, U1804.16
/Channels/RNG2_12: RN208.1, U214.4, U1904.16
/Channels/RNG2_13: RN208.2, U214.5, U2004.16
/Channels/RNG2_14: RN208.3, U214.6, U2104.16
/Channels/RNG2_15: RN208.4, U214.7, U2204.16
/Channels/RNG3_0: RN209.1, U215.15, U704.9
/Channels/RNG3_1: RN209.2, U215.1, U804.9
/Channels/RNG3_2: RN209.3, U215.2, U904.9
/Channels/RNG3_3: RN209.4, U215.3, U1004.9
/Channels/RNG3_4: RN210.1, U215.4, U1104.9
/Channels/RNG3_5: RN210.2, U215.5, U1204.9
/Channels/RNG3_6: RN210.3, U215.6, U1304.9
/Channels/RNG3_7: RN210.4, U215.7, U1404.9
/Channels/RNG3_8: RN211.1, U216.15, U1504.9
/Channels/RNG3_9: RN211.2, U216.1, U1604.9
/Channels/RNG3_10: RN211.3, U216.2, U1704.9
/Channels/RNG3_11: RN211.4, U216.3, U1804.9
/Channels/RNG3_12: RN212.1, U216.4, U1904.9
/Channels/RNG3_13: RN212.2, U216.5, U2004.9
/Channels/RNG3_14: RN212.3, U216.6, U2104.9
/Channels/RNG3_15: RN212.4, U216.7, U2204.9
/FPGA, configuration, range registers/AD_BUSY: U201.T3, U301.67
/FPGA, configuration, range registers/AD_CONVST: U201.T2, U301.68
/FPGA, configuration, range registers/AD_CS_N: U201.P3, U301.63
/FPGA, configuration, range registers/AD_RESET_N: U201.P4, U301.36
/FPGA, configuration, range registers/AD_SCLK: U201.N4, U301.62
/FPGA, configuration, range registers/AD_SDI: U201.R2, U301.55
/FPGA, configuration, range registers/AD_SDOA: U201.R3, U301.57
/FPGA, configuration, range registers/AD_SDOB: U201.R4, U301.56
/FPGA, configuration, range registers/I2C_SCL: J101.233, R236.2, U201.B7, U217.6
/FPGA, configuration, range registers/I2C_SDA: J101.232, R235.2, U201.C7, U217.5
/FPGA, configuration, range registers/LINK_CLK_N: J101.243, U201.J15
/FPGA, configuration, range registers/LINK_CLK_P: J101.242, U201.J16
/FPGA, configuration, range registers/RESET_N: J101.239, R202.2, U201.R9
/FPGA, configuration, range registers/RX0_N: J101.255, U201.C15
/FPGA, configuration, range registers/RX0_P: J101.254, U201.C16
/FPGA, configuration, range registers/RX1_N: J101.258, U201.B15
/FPGA, configuration, range registers/RX1_P: J101.257, U201.B16
/FPGA, configuration, range registers/SA_CLK_N: C481.1, U201.E2
/FPGA, configuration, range registers/SA_CLK_P: C480.1, U201.D1
/FPGA, configuration, range registers/SA_DCO_N: U201.K2, U401.23
/FPGA, configuration, range registers/SA_DCO_P: U201.K1, U401.24
/FPGA, configuration, range registers/SA_FCO_N: U201.K3, U401.25
/FPGA, configuration, range registers/SA_FCO_P: U201.J3, U401.26
/FPGA, configuration, range registers/SB_CLK_N: C581.1, U201.E15
/FPGA, configuration, range registers/SB_CLK_P: C580.1, U201.D16
/FPGA, configuration, range registers/SB_DCO_N: U201.K15, U501.23
/FPGA, configuration, range registers/SB_DCO_P: U201.K16, U501.24
/FPGA, configuration, range registers/SB_FCO_N: U201.K14, U501.25
/FPGA, configuration, range registers/SB_FCO_P: U201.J14, U501.26
/FPGA, configuration, range registers/SC_CSA_N: R485.2, U201.R15
/FPGA, configuration, range registers/SC_CSB_N: R585.2, U201.T15
/FPGA, configuration, range registers/SC_PDWN: R487.2, R587.2, U201.P13
/FPGA, configuration, range registers/SC_SCLK: R481.2, R581.2, U201.N13
/FPGA, configuration, range registers/SC_SDIO: R483.2, R583.2, U201.P14
/FPGA, configuration, range registers/SC_SYNC: R489.2, R589.2, U201.R14
/FPGA, configuration, range registers/SLOT_ID0: J101.235, R232.2, U201.R13, U217.1
/FPGA, configuration, range registers/SLOT_ID1: J101.236, R233.2, U201.T14, U217.2
/FPGA, configuration, range registers/SLOT_ID2: J101.237, R234.2, U201.R12, U217.3
/FPGA, configuration, range registers/TRIG_N: J101.246, U201.F14
/FPGA, configuration, range registers/TRIG_P: J101.245, U201.E14
/FPGA, configuration, range registers/TX0_N: J101.249, U201.C2
/FPGA, configuration, range registers/TX0_P: J101.248, U201.C1
/FPGA, configuration, range registers/TX1_N: J101.252, U201.B2
/FPGA, configuration, range registers/TX1_P: J101.251, U201.B1
/I_FAST0: R410.1, R715.2, R718.1, U707.1
/I_FAST1: R416.1, R815.2, R818.1, U807.1
/I_FAST2: R422.1, R915.2, R918.1, U907.1
/I_FAST3: R428.1, R1015.2, R1018.1, U1007.1
/I_FAST4: R434.1, R1115.2, R1118.1, U1107.1
/I_FAST5: R440.1, R1215.2, R1218.1, U1207.1
/I_FAST6: R446.1, R1315.2, R1318.1, U1307.1
/I_FAST7: R452.1, R1415.2, R1418.1, U1407.1
/I_FAST8: R510.1, R1515.2, R1518.1, U1507.1
/I_FAST9: R516.1, R1615.2, R1618.1, U1607.1
/I_FAST10: R522.1, R1715.2, R1718.1, U1707.1
/I_FAST11: R528.1, R1815.2, R1818.1, U1807.1
/I_FAST12: R534.1, R1915.2, R1918.1, U1907.1
/I_FAST13: R540.1, R2015.2, R2018.1, U2007.1
/I_FAST14: R546.1, R2115.2, R2118.1, U2107.1
/I_FAST15: R552.1, R2215.2, R2218.1, U2207.1
/SA_DN0: U201.J5, U401.33
/SA_DN1: U201.H4, U401.31
/SA_DN2: U201.H2, U401.29
/SA_DN3: U201.G2, U401.27
/SA_DN4: U201.H3, U401.21
/SA_DN5: U201.G4, U401.19
/SA_DN6: U201.E1, U401.17
/SA_DN7: U201.F5, U401.15
/SA_DP0: U201.J4, U401.34
/SA_DP1: U201.H5, U401.32
/SA_DP2: U201.G1, U401.30
/SA_DP3: U201.F1, U401.28
/SA_DP4: U201.G3, U401.22
/SA_DP5: U201.G5, U401.20
/SA_DP6: U201.F2, U401.18
/SA_DP7: U201.F4, U401.16
/SB_DN0: U201.J12, U501.33
/SB_DN1: U201.H13, U501.31
/SB_DN2: U201.H15, U501.29
/SB_DN3: U201.G15, U501.27
/SB_DN4: U201.H14, U501.21
/SB_DN5: U201.G13, U501.19
/SB_DN6: U201.E16, U501.17
/SB_DN7: U201.F12, U501.15
/SB_DP0: U201.J13, U501.34
/SB_DP1: U201.H12, U501.32
/SB_DP2: U201.G16, U501.30
/SB_DP3: U201.F16, U501.28
/SB_DP4: U201.G14, U501.22
/SB_DP5: U201.G12, U501.20
/SB_DP6: U201.F15, U501.18
/SB_DP7: U201.F13, U501.16
GND: C101.2, C102.2, C103.2, C104.2, C105.2, C106.2, C107.2, C108.2, C120.2, C121.2, C122.2, C123.2, C124.2, C125.2, C126.2, C127.2, C130.2, C131.2, C132.2, C133.2, C134.2, C135.2, C140.2, C141.2, C142.2, C150.2, C151.2, C152.2, C153.2, C154.2, C155.2, C160.2, C161.2, C162.2, C163.2, C164.2, C165.2, C201.2, C202.2, C203.2, C204.2, C205.2, C206.2, C207.2, C208.2, C209.2, C210.2, C211.2, C212.2, C213.2, C214.2, C215.2, C216.2, C217.2, C218.2, C219.2, C220.2, C221.2, C222.2, C223.2, C224.2, C225.2, C226.2, C227.2, C228.2, C229.2, C230.2, C231.2, C232.2, C240.1, C241.2, C251.2, C252.2, C253.2, C254.2, C255.2, C256.2, C257.2, C301.2, C302.2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
unnamed: C155.1, R122.2
unnamed: C165.1, R132.2
unnamed: C210.1, C211.1, C212.1, FB201.2, U201.G11, U201.L7
unnamed: C468.1, C469.1, C470.1, FB402.1, U401.14, U401.35
unnamed: C568.1, C569.1, C570.1, FB502.1, U501.14, U501.35
unnamed: C101.1, C102.1, C150.1, C151.1, D101.1, FB101.2, U106.3
unnamed: C103.1, C104.1, C160.1, C161.1, D102.2, FB102.2, U107.2
unnamed: D201.2, R222.1
unnamed: D202.2, R223.1
unnamed: C411.1, D410.3, R414.2, U401.43
unnamed: C460.1, C461.1, C462.1, C463.1, C464.1, C465.1, C466.1, C467.1, D410.2, D411.2, D412.2, D413.2, D414.2, D415.2, D416.2, D417.2, D418.2, D419.2, D420.2, D421.2, D422.2, D423.2, D424.2, D425.2, FB401.1, U401.1, U401.4, U401.7, U401.8, U401.11, U401.12, U401.37, U401.42, U401.45, U401.48, U401.51, U401.59, U401.62
unnamed: C411.2, D411.3, R415.2, U401.44
unnamed: C414.1, D412.3, R420.2, U401.47
unnamed: C414.2, D413.3, R421.2, U401.46
unnamed: C417.1, D414.3, R426.2, U401.49
unnamed: C417.2, D415.3, R427.2, U401.50
unnamed: C420.1, D416.3, R432.2, U401.53
unnamed: C420.2, D417.3, R433.2, U401.52
unnamed: C423.1, D418.3, R438.2, U401.60
unnamed: C423.2, D419.3, R439.2, U401.61
unnamed: C426.1, D420.3, R444.2, U401.64
unnamed: C426.2, D421.3, R445.2, U401.63
unnamed: C429.1, D422.3, R450.2, U401.2
unnamed: C429.2, D423.3, R451.2, U401.3
unnamed: C432.1, D424.3, R456.2, U401.6
unnamed: C432.2, D425.3, R457.2, U401.5
unnamed: C511.1, D510.3, R514.2, U501.43
unnamed: C560.1, C561.1, C562.1, C563.1, C564.1, C565.1, C566.1, C567.1, D510.2, D511.2, D512.2, D513.2, D514.2, D515.2, D516.2, D517.2, D518.2, D519.2, D520.2, D521.2, D522.2, D523.2, D524.2, D525.2, FB501.1, U501.1, U501.4, U501.7, U501.8, U501.11, U501.12, U501.37, U501.42, U501.45, U501.48, U501.51, U501.59, U501.62
unnamed: C511.2, D511.3, R515.2, U501.44
unnamed: C514.1, D512.3, R520.2, U501.47
unnamed: C514.2, D513.3, R521.2, U501.46
unnamed: C517.1, D514.3, R526.2, U501.49
unnamed: C517.2, D515.3, R527.2, U501.50
unnamed: C520.1, D516.3, R532.2, U501.53
unnamed: C520.2, D517.3, R533.2, U501.52
unnamed: C523.1, D518.3, R538.2, U501.60
unnamed: C523.2, D519.3, R539.2, U501.61
unnamed: C526.1, D520.3, R544.2, U501.64
unnamed: C526.2, D521.3, R545.2, U501.63
unnamed: C529.1, D522.3, R550.2, U501.2
unnamed: C529.2, D523.3, R551.2, U501.3
unnamed: C532.1, D524.3, R556.2, U501.6
unnamed: C532.2, D525.3, R557.2, U501.5
unnamed: FB101.1, J101.2, J101.3, J101.146, J101.147
unnamed: FB102.1, J101.5, J101.6, J101.149, J101.150
unnamed: FB103.1, J101.8, J101.9, J101.10, J101.152, J101.153, J101.154
unnamed: FB104.1, J101.12, J101.13, J101.14, J101.156, J101.157, J101.158
unnamed: J201.3, R214.1, U201.T10
unnamed: J201.5, R212.2, U201.R11
unnamed: J201.4, R213.2, U201.M10
unnamed: J201.6, R211.2, U201.T11
unnamed: R110.2, U101.1
unnamed: R111.2, R112.1, U101.5
unnamed: L101.1, U101.3
unnamed: R113.2, U102.1
unnamed: R114.2, R115.1, U102.5
unnamed: L102.1, U102.3
unnamed: C152.1, R120.2, R121.1, U106.1
unnamed: C162.1, R130.2, R131.1, U107.1
unnamed: U201.C6, U211.14
unnamed: U201.B6, U211.11, U212.11, U213.11, U214.11, U215.11, U216.11
unnamed: U201.E7, U211.12, U212.12, U213.12, U214.12, U215.12, U216.12
unnamed: R231.2, U201.D7, U211.13, U212.13, U213.13, U214.13, U215.13, U216.13
unnamed: R221.1, U201.P6
unnamed: R205.2, R220.1, U201.N9
unnamed: R201.2, U201.P10
unnamed: R204.2, U201.P9
unnamed: R203.2, U201.T9
unnamed: R223.2, U201.T6
unnamed: R222.2, U201.R6
unnamed: R210.2, U201.N7, U202.7
unnamed: R209.2, U201.M7, U202.3
unnamed: R208.2, U201.T7, U202.2
unnamed: R207.2, U201.T8, U202.5
unnamed: R206.2, U201.N8, U202.1
unnamed: R220.2, U202.6
unnamed: U211.9, U212.14
unnamed: U212.9, U213.14
unnamed: U213.9, U214.14
unnamed: U214.9, U215.14
unnamed: U215.9, U216.14
unnamed: C302.1, U301.31
unnamed: C301.1, U301.33
unnamed: C303.1, U301.70
unnamed: C304.1, U301.52
unnamed: R301.2, U301.27
unnamed: R309.2, U301.74
unnamed: R302.2, U301.25
unnamed: R310.2, U301.76
unnamed: R303.2, U301.23
unnamed: R311.2, U301.78
unnamed: R304.2, U301.21
unnamed: R312.2, U301.80
unnamed: R305.2, U301.20
unnamed: R313.2, U301.1
unnamed: R306.2, U301.18
unnamed: R314.2, U301.3
unnamed: R307.2, U301.13
unnamed: R315.2, U301.8
unnamed: R308.2, U301.11
unnamed: R316.2, U301.10
unnamed: C480.2, R480.1, U401.10
unnamed: C481.2, R480.2, U401.9
unnamed: R485.1, R486.1, U401.40
unnamed: R487.1, R488.1, U401.41
unnamed: R492.1, U401.54
unnamed: R481.1, R482.1, U401.38
unnamed: R483.1, R484.1, U401.39
unnamed: R489.1, R490.1, U401.58
unnamed: C493.1, U401.57, U402.3
unnamed: C490.1, C491.1, U401.56
unnamed: C495.1, R494.1, U402.1, U402.2, U403.5, U404.5, U405.5, U406.5, U407.5, U408.5, U409.5, U410.5
unnamed: R494.2, R495.1, U402.5
unnamed: C496.1, U402.6, U402.7, U403.3, U404.3, U405.3, U406.3, U407.3, U408.3, U409.3, U410.3
unnamed: C410.1, R410.2, R411.1, U403.2
unnamed: C410.2, R411.2, R412.1, R415.1, U403.1
unnamed: R412.2, R413.1, U403.6
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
